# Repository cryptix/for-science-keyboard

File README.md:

<!--
SPDX-FileCopyrightText: 2021 Paul James <p.james@coolblue.nl>

SPDX-License-Identifier: CC0-1.0
-->

[![License: MIT](
https://img.shields.io/badge/License-MIT-blue.svg)](
https://choosealicense.com/licenses/mit/)
[![REUSE status](
https://api.reuse.software/badge/github.com/peej/for-science-keyboard)](
https://api.reuse.software/info/github.com/peej/for-science-keyboard)
[![made-with-Markdown](
https://img.shields.io/badge/Made%20with-Markdown-1f425f.svg)](
http://commonmark.org)

*For Science* is a 46 key ortholinear split keyboard PCB with a 3 key thumb cluster.

The goal of this project is to build a usable split keyboard with a PCB case
within the 100x100mm cheap PCB size limit offered by some PCB manufacturers.
Designed to be easy to build,
it only supports serial communication over a TRRS cable and no LEDs.
The PCB is reversible,
meaning that you need two of the same PCB to create a full keyboard.

# Bill of Materials (BOM)

* 2 PCBs
* 46 MX compatible switches.
* 46 1n4148 diodes.
* 2 Pro Micro controllers.
* 2 PJ320D 3.5mm TRRS jacks.
* TRRS cable and micro USB cable.
* 2 plate PCBs and 2 base PCBs.
* 8 2M standoffs
* 16 2M screws
* 46 MX compatible key caps.

# Ordering PCBs

PCBs can be manufactured by a variety of online PCB fabricators.
Some have special offers for PCBs under 100mm square,
so shop around.
You can use [PCBShopper](https://pcbshopper.com/) to search for the best price.

The 3 ZIP files in the */gerber* directory contain the Gerber files your fabricator will need to make:

* main PCB [for-science-pcb.zip](
  https://github.com/peej/for-science-keyboard/blob/master/gerber/for-science-pcb.zip)
* plate [for-science-plate.zip](
  https://github.com/peej/for-science-keyboard/blob/master/gerber/for-science-plate.zip)
* base PCB [for-science-base.zip](
  https://github.com/peej/for-science-keyboard/blob/master/gerber/for-science-base.zip)

When uploading the Gerber ZIP files,
use the default PCB settings.
The plate PCB thickness should be 1.6mm for the switches to snap into the plate securely.

# Construction

* Solder the diodes onto the underside of each PCB
* Solder on the Pro Micro headers (or a 24 pin DIP socket) onto the underside of each PCB.
  Do not solder on the Pro Micros yet
* Solder the PJ320D TRRS sockets onto the underside of each PCB.
  These are SMD components rather than through-hole,
  so as not to interfere with the switch locations
* Insert the switches into the plate and then into the top of the PCBs.
  Insert all the switches and ensure that the pins of each switch
  are correctly coming through the board and are not bent under the PCB
* Solder all the switch pins
* Solder on the Pro Micros.
  Ensure that you get them the correct way around
  and with the correct side up.
  The chip side should be face down on the left hand PCB
  and face up on the right hand PCB
* Attach the standoffs to the plate PCB with the screws
* Attach the base to the standoffs
* Connect the halves together with the TRRS cable
* Flash both Pro Micros with the firmware,
  see the [QMK documentation](http://qmk.fm/)
  on how to build and flash the firmware

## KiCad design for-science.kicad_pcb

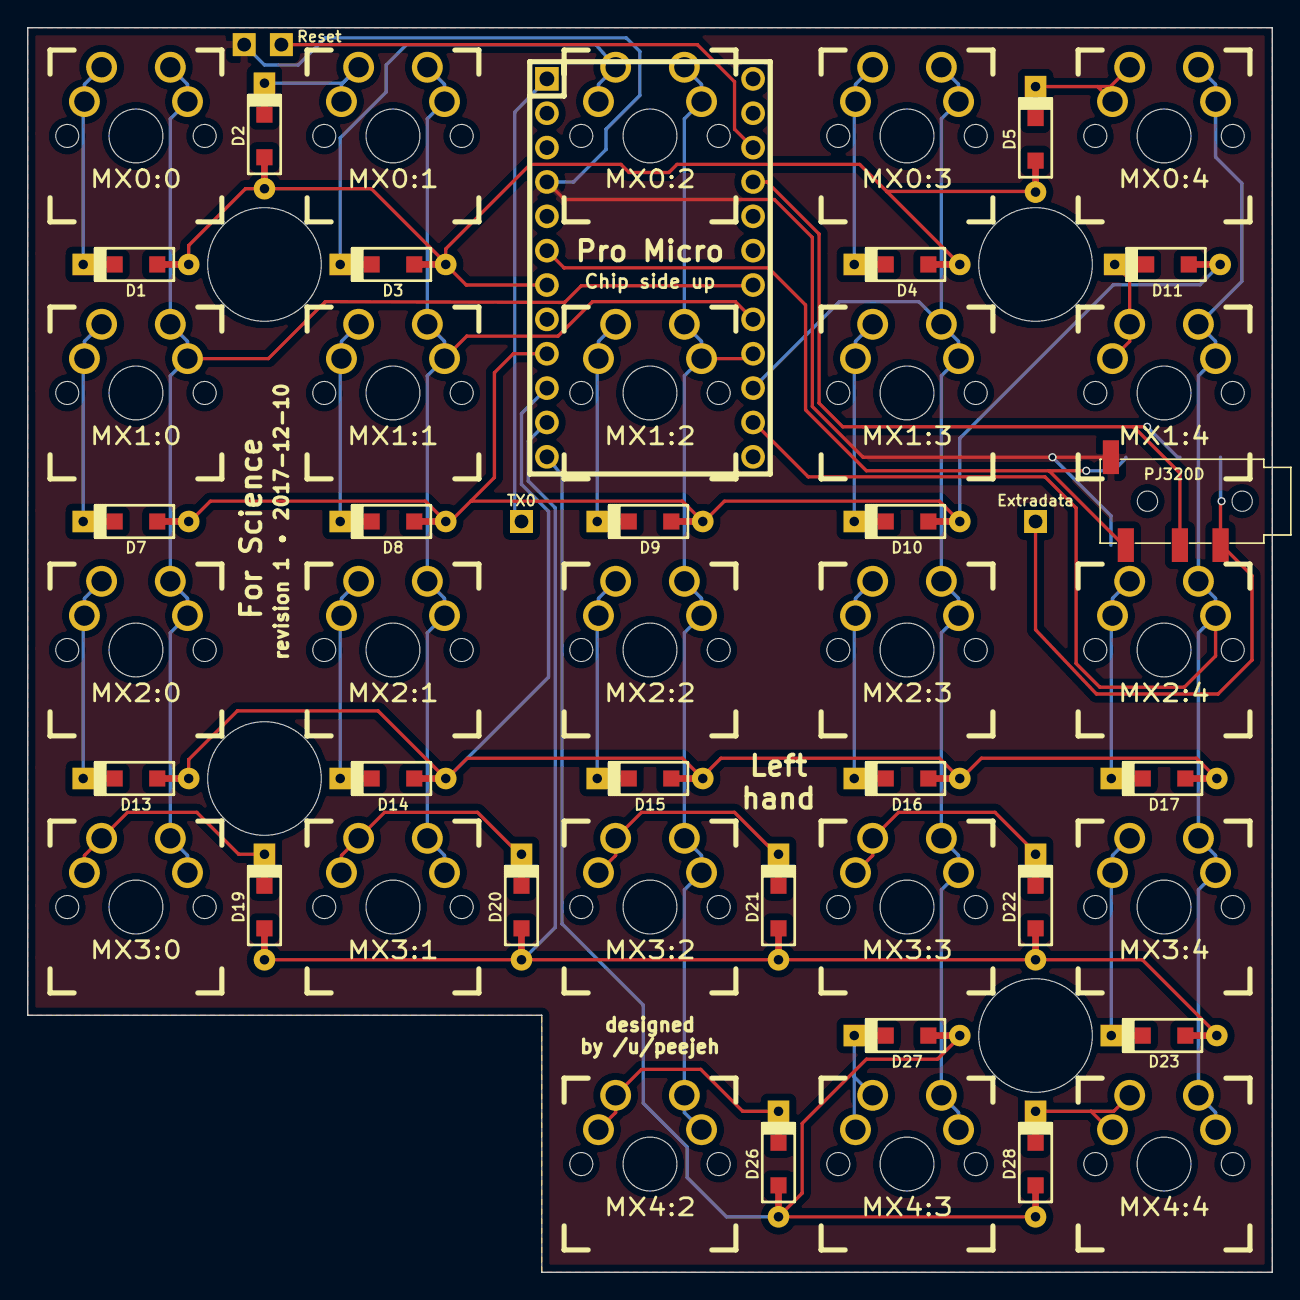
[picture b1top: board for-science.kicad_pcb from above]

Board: 2 copper layers, 92.0 x 92.0 mm, 57 parts (1 on the bottom side), 39 nets.

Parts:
D1, D2, D3, D4, D5, D7, D8, D9, D10, D11, D13, D14, D15, D16, D17, D19, D20, D21, D22, D23, D26, D27, D28: DIODE; D_SOD123_axial
EXTRADATA1: Extradata; PIN_1_SQUARE
GROUND1: Ground; PIN_1_SQUARE
J1: TRRS; PJ320D_3.5mm_Jack_SMD
J2: TRRS; PJ320D_3.5mm_Jack_SMD_Flip
M8, M8#2, M8#3, M8#4: MountingHole_8.4mm_M8
MX0:0: MX0:9; MX_DoubleSided
MX0:1: MX0:8; MX_DoubleSided
MX0:2: MX0:7; MX_DoubleSided
MX0:3: MX0:6; MX_DoubleSided
MX0:4: MX0:5; MX_DoubleSided
MX1:0: MX1:9; MX_DoubleSided
MX1:1: MX1:8; MX_DoubleSided
MX1:2, MX1:4: MX1:7; MX_DoubleSided
MX1:3: MX1:6; MX_DoubleSided
MX2:0: MX2:9; MX_DoubleSided
MX2:1: MX2:8; MX_DoubleSided
MX2:2: MX2:7; MX_DoubleSided
MX2:3: MX2:6; MX_DoubleSided
MX2:4: MX2:5; MX_DoubleSided
MX3:0: MX3:9; MX_DoubleSided
MX3:1: MX3:8; MX_DoubleSided
MX3:2: MX3:7; MX_DoubleSided
MX3:3: MX3:6; MX_DoubleSided
MX3:4: MX3:5; MX_DoubleSided
MX4:2: MX4:7; MX_DoubleSided
MX4:3: MX4:6; MX_DoubleSided
MX4:4: MX4:5; MX_DoubleSided
RESET1: Reset; PIN_1_SQUARE
TX0: TX0; PIN_1_SQUARE
U1: ARDUINO_PRO_MICRO

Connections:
/Col0: MX0:0.1, MX1:0.1, MX2:0.1, MX3:0.1, U1.18
/Col1: MX0:1.1, MX1:1.1, MX2:1.1, MX3:1.1, U1.17
/Col2: MX0:2.1, MX1:2.1, MX2:2.1, MX3:2.1, MX4:2.1, U1.16
/Col3: MX0:3.1, MX1:3.1, MX2:3.1, MX3:3.1, MX4:3.1, U1.15
/Col4: MX0:4.1, MX1:4.1, MX2:4.1, MX3:4.1, MX4:4.1, U1.14
/Row0: D1.2, D2.2, D3.2, D4.2, D5.2, U1.7
/Row1: D7.2, D8.2, D9.2, D10.2, D11.2, U1.9
/Row2: D13.2, D14.2, D15.2, D16.2, D17.2, U1.10
/Row3: D19.2, D20.2, D21.2, D22.2, D23.2, U1.11
/Row4: D26.2, D27.2, D28.2, U1.12
GND: GROUND1.1, J1.4, J2.4, U1.4
unnamed: D1.1, MX0:0.2
unnamed: D2.1, MX0:1.2
unnamed: D3.1, MX0:2.2
unnamed: D4.1, MX0:3.2
unnamed: D5.1, MX0:4.2
unnamed: D7.1, MX1:0.2
unnamed: D8.1, MX1:1.2
unnamed: D9.1, MX1:2.2
unnamed: D10.1, MX1:3.2
unnamed: D11.1, MX1:4.2
unnamed: D13.1, MX2:0.2
unnamed: D14.1, MX2:1.2
unnamed: D15.1, MX2:2.2
unnamed: D16.1, MX2:3.2
unnamed: D17.1, MX2:4.2
unnamed: D19.1, MX3:0.2
unnamed: D20.1, MX3:1.2
unnamed: D21.1, MX3:2.2
unnamed: D22.1, MX3:3.2
unnamed: D23.1, MX3:4.2
unnamed: D26.1, MX4:2.2
unnamed: D27.1, MX4:3.2
unnamed: D28.1, MX4:4.2
unnamed: EXTRADATA1.1, J1.3, J2.3
unnamed: J1.1, J2.1, U1.6
unnamed: RESET1.1, U1.22
unnamed: TX0.1, U1.1
VCC: J1.2, J2.2, U1.21

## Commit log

2017-12-20 Add gerber files
    Former-commit-id: ffd29a30d6e1f60fa59137906bac824ee8369ceb
2017-12-21 Updated readme with construction information
    Former-commit-id: 4445529d90c039263eda5d83002c5c334f22aad8
2018-02-06 Add assembled keyboard picture
    Former-commit-id: 4cb12e38262253e15162c06579b20d56226f6bdf
2020-08-07 README: two typos and a few minor formatting changes
    Former-commit-id: a552e573dd6f3f94677986fad71d4067ba2f505a
2020-08-07 README: reflow text
    Former-commit-id: c49f690db31f759d66fe902ddba7f040a4767dee
2020-08-28 git ignore /fp-info-cache
    Former-commit-id: 7c2e61d03b290d71a9d49541e28b171d0541b06e
2020-08-31 git ignore `/build/`
2020-08-31 base: Adds OSEG logo and meta-data
    * Source (fixed, manual value)
    * License (fixed, manual value)
    * Version (placeholder, missing replacement method!)
    * Version-Date (placeholder, missing replacement method!)
    * Manufacturer (fixed, manual value)
    * Manufacturer-Serial-Number (placeholder, filled in by manufacturer)
2020-09-08 CI: Try to generate Gerbers & co with KiBot
2020-09-08 CI: ... also for the oseg branch
2020-09-08 Adds KiBot config files
2020-09-09 Update SCH from KiCad v2 to v5
2020-09-09 CI: KiBot: Unuse non-existent BoM fields [fix]
2020-09-09 CI: KiBot: modernize & fixup a bit
2020-09-09 CI: KiBot: Re-run when workflow/action changes
2020-09-26 CI: KiBot: Check zone fills
2020-09-26 base: Adds more meta-data varables
2020-09-26 CI: Also builds for the oseg branch
2020-09-26 CI: Set out-dir 'build'
2020-09-28 Add legacy symbols-table stuff
2020-09-28 Git ignore more KiCad backup files
2020-09-28 CI: Use new, separate Makefile for building
2020-09-28 CI: Make commands compatible with original `sh` [fix]
2020-09-28 Revert "CI: Make commands compatible with original `sh` [fix]"
    This reverts commit 6f02eee12ce0558494f581d8f3cef7eb1d94d140.
2020-09-28 CI: Correctly checking for source-files existence [fix]
2020-10-13 Makefile: Process all PCB and Schematics files & minor fixes
2020-10-13 Makefile: create build directory [fix]
2020-10-13 CI: build more often
2020-11-08 make: Specify inputs rigourosly & per-board config
2020-11-08 TMP Check if good (auto-updated for-science fills)
2021-07-10 static configs for boards with and without sch
2021-07-10 Adds the "without-sch" config
2021-07-10 Improve licensing info (REUSE/SPDX compatible)
2021-07-10 README: Add badges: License, REUSE, made-with-markdown
2021-07-10 Makefile: Adds some BASH error handling
2021-08-10 TMP adds 5 rectangles for image injector
2021-10-10 TMP CI: Try to generate everything
2021-10-10 TMP CI: Try projvar & generate qr-code on the fly
2021-10-10 CI: Use fixed versions of projvar and kicad-text-injector
2021-10-11 CI: Adds a kicad-image-injector dependency [fix]
2021-10-11 CI: Projvar related workarounds
2021-10-11 CI: Use projvar 0.4.3 [fix]
2021-10-11 CI: TMP Try debugging ...
2021-10-12 CI: Debugging cleanup
2021-10-12 Update PCB with var names form projvar
2021-10-12 CI: projvar updates & related
2021-10-13 CI: Lots of updates!
2021-10-13 CI: Fixes version fetching [fix]
2021-10-13 Documents value in manually set projvars.env [minor]
2021-10-14 CI: Moves instructions to a separate script
2021-10-15 CI: KiBot config: generate 2D renders as PNGs, not JPGs
2021-10-15 CI: Adds a comment to GH action file [minor]
2021-10-15 Changes deps install short option flag from -s to -i
2021-10-15 add CLI flag --short (skips KiBot and archiving part)
2021-10-15 CI: Puts temp file into build dir [fix]
2021-10-15 CI: Remove previous build
2021-10-15 CI: Also install KiBot and deps
    Instructions copied form the KiBot and KiAuto Dockerfile's
2021-12-10 fix typos in github actions
    jobs names and output of DRC and ERC were switched
2021-12-21 use tools from new image
2021-12-21 remove apt steps
2021-12-21 just print the vars
